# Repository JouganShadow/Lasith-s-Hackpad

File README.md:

# Lasith-s-Hackpad
Hackpad for Hack club

BOM: 
- 9x Cherry MX Switches
- 6x SK6812 MINI Leds
- 1x XIAO RP2040
- 9x Blank DSA Keycaps
- 4x M3x16 Bolt
- 4x M3 Heatset
- 1 3D-printed case

Others:

- KMK Firmware

- All the necessary .STEP files are there in the CAD folder

### Inspiration

The main inspiration was that I'm going to pursue Com. science in the future and I was really looking forward to making something like this, the reason I couldnt so far was due to lack of funds, but as soon as I got to know that Hack Club is giving this amazing opportunity I got on my computer and started working on it. The main challenge for this project was that I got to know about it just a day before the due date, but thanks to the inspiring message Mr. Clay the co-founder of hack club blueprint I kept on working on it and finally finished it. This is also my first time using any of these softwares like Kicad and fusion, but thanks to the tutorial I managed to pull through. Thanks a lot to everyone at Hack club!

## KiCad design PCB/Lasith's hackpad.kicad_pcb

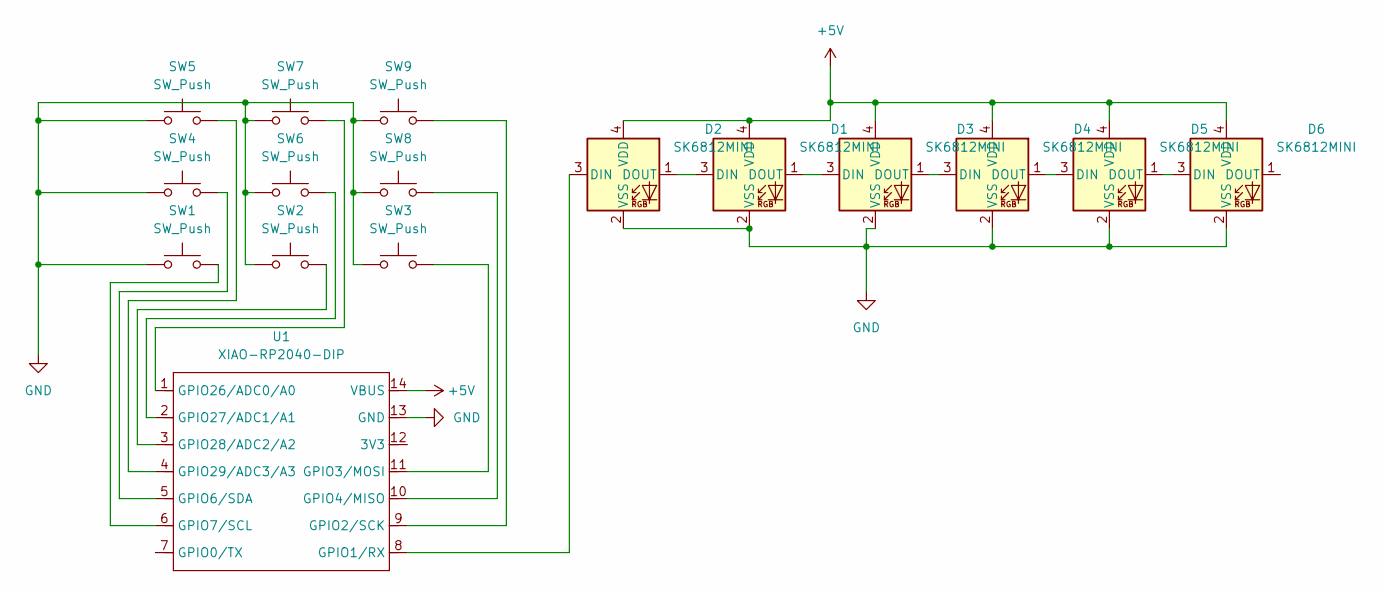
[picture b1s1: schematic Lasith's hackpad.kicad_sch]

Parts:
D1, D2, D3, D4, D5, D6: SK6812MINI; LED_SK6812MINI_PLCC4_3.5x3.5mm_P1.75mm
SW1, SW2, SW3, SW4, SW5, SW6, SW7, SW8, SW9: SW_Push; SW_Cherry_MX_1.00u_PCB
U1: XIAO-RP2040-DIP

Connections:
+5V: D1.4 (VDD), D2.4 (VDD), D3.4 (VDD), D4.4 (VDD), D5.4 (VDD), D6.4 (VDD), U1.14 (VBUS)
GND: D1.2 (VSS), D2.2 (VSS), D3.2 (VSS), D4.2 (VSS), D5.2 (VSS), D6.2 (VSS), SW1.1, SW2.1, SW3.1, SW4.1, SW5.1, SW6.1, SW7.1, SW8.1, SW9.1, U1.13 (GND)
unnamed: D1.3 (DIN), D2.1 (DOUT)
unnamed: D1.1 (DOUT), D3.3 (DIN)
unnamed: D2.3 (DIN), U1.8 (GPIO1/RX)
unnamed: D3.1 (DOUT), D4.3 (DIN)
unnamed: D4.1 (DOUT), D5.3 (DIN)
unnamed: D5.1 (DOUT), D6.3 (DIN)
unnamed: SW9.2, U1.9 (GPIO2/SCK)
unnamed: SW3.2, U1.11 (GPIO3/MOSI)
unnamed: SW8.2, U1.10 (GPIO4/MISO)
unnamed: SW4.2, U1.5 (GPIO6/SDA)
unnamed: SW1.2, U1.6 (GPIO7/SCL)
unnamed: SW7.2, U1.1 (GPIO26/ADC0/A0)
unnamed: SW6.2, U1.2 (GPIO27/ADC1/A1)
unnamed: SW2.2, U1.3 (GPIO28/ADC2/A2)
unnamed: SW5.2, U1.4 (GPIO29/ADC3/A3)

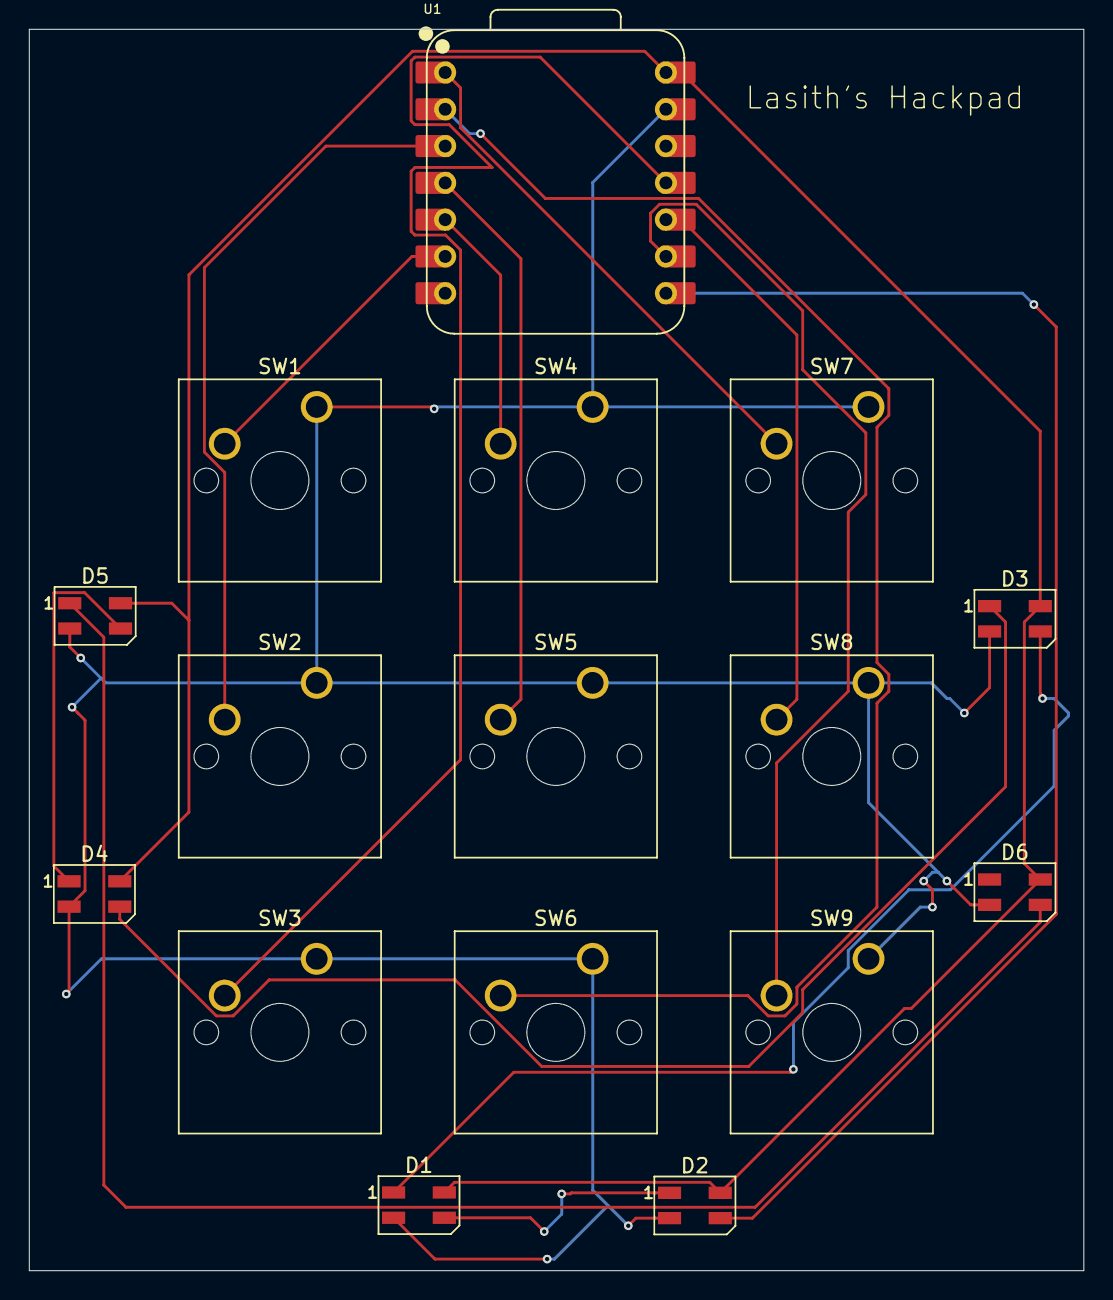
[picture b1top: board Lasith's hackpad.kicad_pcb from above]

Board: 2 copper layers, 72.8 x 85.7 mm, 16 parts (0 on the bottom side), 17 nets.

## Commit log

2025-12-04 Create main.py
    the firmware
2025-12-04 Create null
